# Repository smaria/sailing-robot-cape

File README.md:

sailing-robot-cape
==================

BeagleBone Black cape for the autonomous sailing robot

Issues in v1 that need to be corrected:
- Capacitors for linear regulator need to be added;
        ca. 100nF on both sides 
        and additional ca. 100uF on Vin 
        to protect batteries from high current peaks
- attention with wires that go through pin headers, if the pcb is etched
- Avoid the eMMC and HDMI (LCD) pins
- consider choosing other PWM pins? (see boat servo sail logs, PWM1A and PWM2A
  are probably the safer bets for functioning servo control
- GPS1 and SDA signal overlap near the solder jumper!!
- power supply should be switched to a switching power supply,
  since linear regulators heat up too much (and loose a high amount of energy in the process)
  in this process the servo motors power supply is separated from the BBB power
- power supply needs a bit wider/better spacing

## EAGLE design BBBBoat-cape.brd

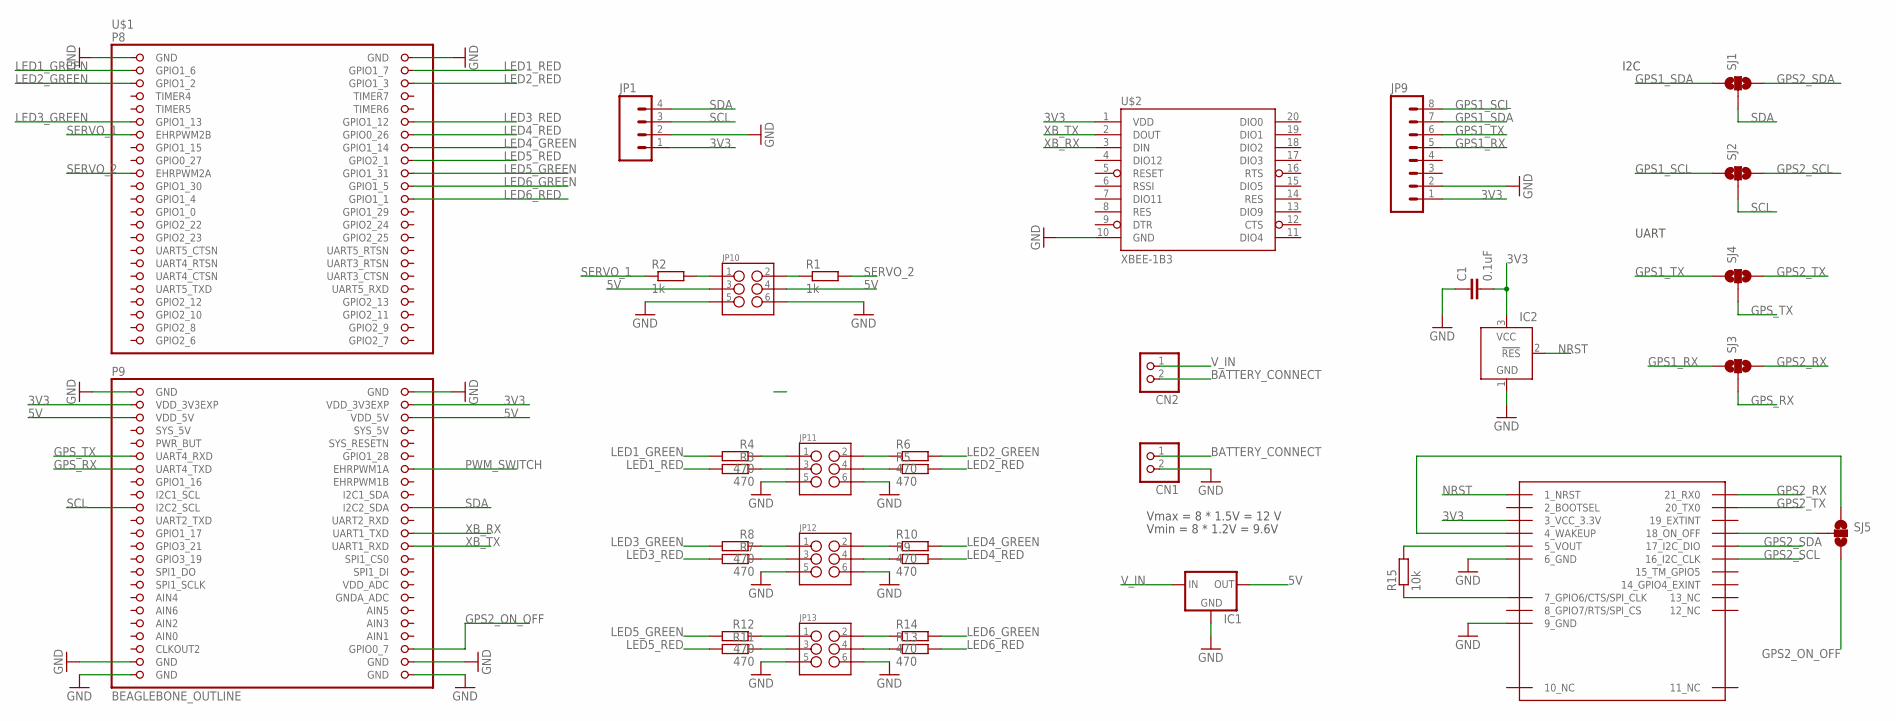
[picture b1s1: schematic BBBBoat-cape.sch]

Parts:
C1: 0.1uF; 0603-CAP
CN1, CN2: JST_2PIN-SMT; JST-PH-2-SMT
IC1: V_REG_78XX-TO-220; TO-220-ALT
IC2: TCM809; SOT23B-3
JP1: M04SMD_STRAIGHT_COMBO; 1X04_SMD_STRAIGHT_COMBO
JP9: M08SMD-MALE; 1X08_SMD_MALE
JP10, JP11, JP12, JP13: M03X2; 2X3_SMD
R1, R2: 1k; 0204/7
R3, R4, R5, R6, R7, R8, R9, R10, R11, R12, R13, R14: 470; 0204/7
R15: 10k; 0204/7
SJ1, SJ2, SJ3, SJ4, SJ5: SOLDERJUMPER_2WAYT; SJ_2
U$1: BEAGLEBONE_OUTLINE; BEAGLEBONE_SHIELD
U$2: XBEE-1B3; XBEE-SMD
U$3: A2035-H; A2035H

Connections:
3V3: C1.2, IC2.3 (VCC), JP1.1, JP9.1, U$1.49 (VDD_3V3EXP), U$1.50 (VDD_3V3EXP), U$2.1 (VDD), U$3.3_VCC_3.3V
5V: IC1.OUT, JP10.3, JP10.4, U$1.51 (VDD_5V), U$1.52 (VDD_5V)
AIN0: U$1.85 (AIN0)
BATTERY_CONNECT: CN1.1 (2), CN2.2 (1)
GND: C1.1, CN1.2 (1), IC1.GND, IC2.1 (GND), JP1.2, JP9.2, JP10.5, JP10.6, JP11.5, JP11.6, JP12.5, JP12.6, JP13.5, JP13.6, U$1.1 (GND), U$1.2 (GND), U$1.47 (GND), U$1.48 (GND), U$1.89 (GND), U$1.90 (GND), U$1.91 (GND), U$1.92 (GND), U$2.10 (GND), U$3.6_GND, U$3.9_GND
GPS1_RX: JP9.5, SJ3.1
GPS1_SCL: JP9.8, SJ2.1
GPS1_SDA: JP9.7, SJ1.1
GPS1_TX: JP9.6, SJ4.1
GPS2_ON_OFF: SJ5.3, U$1.88 (GPIO0_7)
GPS2_RX: SJ3.3, U$3.21_RX0
GPS2_SCL: SJ2.3, U$3.16_I2C_CLK
GPS2_SDA: SJ1.3, U$3.17_I2C_DIO
GPS2_TX: SJ4.3, U$3.20_TX0
GPS_RX: SJ3.2, U$1.59 (UART4_TXD)
GPS_TX: SJ4.2, U$1.57 (UART4_RXD)
LED1_GREEN: R4.2, U$1.3 (GPIO1_6)
LED1_RED: R3.2, U$1.4 (GPIO1_7)
LED2_GREEN: R6.2, U$1.5 (GPIO1_2)
LED2_RED: R5.2, U$1.6 (GPIO1_3)
LED3_GREEN: R8.2, U$1.11 (GPIO1_13)
LED3_RED: R7.2, U$1.12 (GPIO1_12)
LED4_GREEN: R10.2, U$1.16 (GPIO1_14)
LED4_RED: R9.2, U$1.14 (GPIO0_26)
LED5_GREEN: R12.2, U$1.20 (GPIO1_31)
LED5_RED: R11.2, U$1.18 (GPIO2_1)
LED6_GREEN: R14.2, U$1.22 (GPIO1_5)
LED6_RED: R13.2, U$1.24 (GPIO1_1)
unnamed: JP11.3, R3.1
unnamed: JP11.1, R4.1
unnamed: JP11.4, R5.1
unnamed: JP11.2, R6.1
unnamed: JP12.3, R7.1
unnamed: JP12.1, R8.1
unnamed: JP12.4, R9.1
unnamed: JP12.2, R10.1
unnamed: JP13.3, R11.1
unnamed: JP13.1, R12.1
unnamed: JP13.4, R13.1
unnamed: JP13.2, R14.1
unnamed: R15.1, U$3.7_GPIO6/CTS/SPI_CLK
unnamed: JP10.2, R1.1
unnamed: R15.2, U$3.5_VOUT
unnamed: JP10.1, R2.2
unnamed: SJ5.2, U$3.18_ON_OFF
unnamed: SJ5.1, U$3.4_WAKEUP
NRST: IC2.2 (!RES), U$3.1_NRST
PWM_SWITCH: U$1.60 (EHRPWM1A)
SCL: JP1.3, SJ2.2, U$1.65 (I2C2_SCL)
SDA: JP1.4, SJ1.2, U$1.66 (I2C2_SDA)
SERVO_1: R2.1, U$1.13 (EHRPWM2B)
SERVO_2: R1.2, U$1.19 (EHRPWM2A)
SYS_5V: U$1.53 (SYS_5V)
V_IN: CN2.1 (2), IC1.IN
XB_RX: U$1.70 (UART1_TXD), U$2.3 (DIN)
XB_TX: U$1.72 (UART1_RXD), U$2.2 (DOUT)

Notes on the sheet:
Vmax = 8 * 1.5V = 12 V
Vmin = 8 * 1.2V = 9.6V
I2C
UART

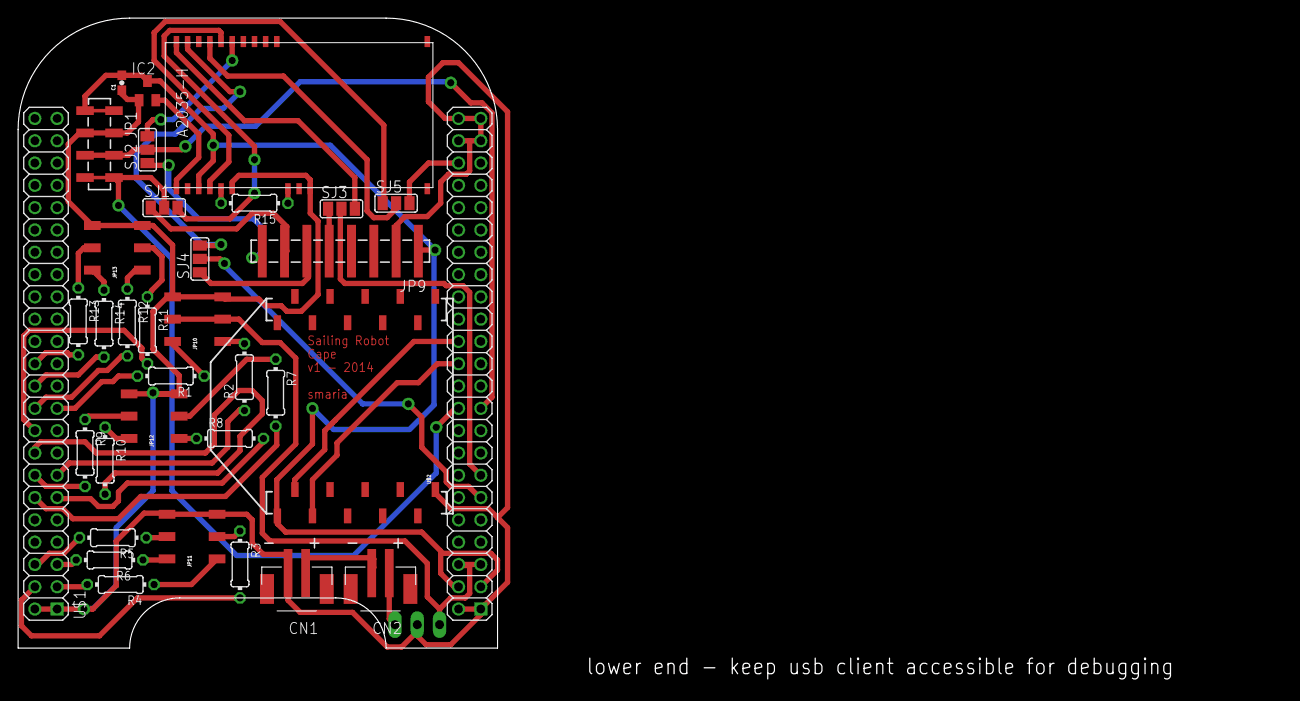
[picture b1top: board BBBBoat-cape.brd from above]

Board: 2 copper layers, 143.9 x 75.7 mm, 34 parts (1 on the bottom side), 53 nets.

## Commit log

2014-08-10 add eagle files that are being made now
    BBBBoat cape v1, as they are being etched right now
    Since its only a one sided etch without vias, most parts were chosen
    to be smd
2014-08-10 mirrored top side for etching
2014-08-10 partlist for the sailing robot cape
2014-08-14 mark arrived parts
2014-08-14 correct jst smd connector part number
    the ordered connector is the wrong type,
    it is flat on the pcb when it should be standing up
2014-08-14 add notes what will be improved in this branch
2014-08-15 fix ridiculous units
2014-08-15 add gps library part
2014-08-18 correct DC/DC converter
    the linear regulators heat up too much/need to large heat sinks
    so they are replaced with a switching regulator
2014-08-19 avoid certain pins if possible
2014-08-20 change PWM pin
    the pwm B pins currently don't work in the PyBBIO library
    so PWM2B was switched to PWM1A
2014-08-21 add gitignore for eagle files
2014-08-21 add notes on PWM, signal overlap on PCB, 5v supply
2014-08-21 add detail on servo motor power supply

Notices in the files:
parts and their libraries:
SparkFun-RF: Licensing: Creative Commons ShareAlike 4.0 International - https://creativecommons.org/licenses/by-sa/4.0
